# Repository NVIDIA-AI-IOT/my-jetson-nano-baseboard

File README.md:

# My Jetson Nano Baseboard

This basic baseboard gives the user the foundation and the flexibility to design their own baseboard for the Jetson Nano. It also repurposes some of the Jetson Nano’s interface signals for simple beginner projects.

This baseboard, as designed, contains:
* A 5V, 4A DC barrel jack
* 4 USB 2.0 connectors
* An HDMI connector
* A UART-to-USB bridge
* A debug USB
* A 40-pin GPIO
* A servo header
* Three user-interactive buttons (power, reset, and force recovery)
* A flex connector for an OLED display

Use these files to kickstart your own application-specific baseboard or implement some quick and easy projects!

## Quick Start

You only need a computer to get started right now! For a more in-depth setup guide, check out `docs/setup.md`.
1.	Install the appropriate version of KiCAD, an open source schematic and layout design program, for your operating system [here](https://www.kicad.org/download/).
1.	Download this GitHub repository either as a ZIP or on the command line.
1.	Save the following symbol and footprint libraries to the “Design Files/Libraries” folder (you may have to make an account – alternatively, if you want the practice, you could try making them yourself):
	1.	[B3SL-1002P](https://octopart.com/b3sl-1002p-omron-9515385)
	1.	[TPD4E02B04DQAR](https://www.snapeda.com/parts/TPD4E02B04DQAR/Texas%20Instruments/view-part/)
	1.	[3-1734592-0](https://www.te.com/usa-en/product-3-1734592-0.html)
	1.	[DC-005-2.0A](https://www.snapeda.com/parts/DC-005/Best%20Inc./view-part/)
	1.	[ACM2012-201-2P-T001](https://www.snapeda.com/parts/ACM2012-201-2P-T001/TDK/view-part/1217094/)
	1.	[10029449-111RLF](https://octopart.com/10029449-111rlf-amphenol+icc+%2F+fci-90332945#CadModels)
	1.	[2309413-1](https://www.te.com/usa-en/product-2309413-1.html)

1.	Open the project (.pro) file in KiCAD.
1.	Add the symbol and footprint libraries as project-specific to your KiCAD program, following [this guide](https://support.snapeda.com/en/articles/2651507-how-to-import-into-kicad). You will know that the libraries are correctly loaded when there are no more boxes with question marks.
1.	You are now set up to tinker with the files and launch your own hardware designs!

Be sure to download the Jetson Nano Product Design Guide [here](https://developer.nvidia.com/embedded/downloads) (NVIDIA Developer account required) to help you with your design.

If you want to make your boards and test them, you’ll need the Jetson Nano module (not included, can be bought as part of the developer kit [here](https://developer.nvidia.com/embedded/jetson-nano-developer-kit)). It is also helpful to have electronics equipment like an oscilloscope, a multimeter, and a soldering iron.

## Questions and Improvements

If you have a suggestion, please open an [issue](https://github.com/NVIDIA-AI-IOT/my-jetson-nano-baseboard/issues/new) on GitHub.

Please share your projects with us on the [Jetson Developer Forums](https://forums.developer.nvidia.com/c/agx-autonomous-machines/jetson-embedded-systems/70).

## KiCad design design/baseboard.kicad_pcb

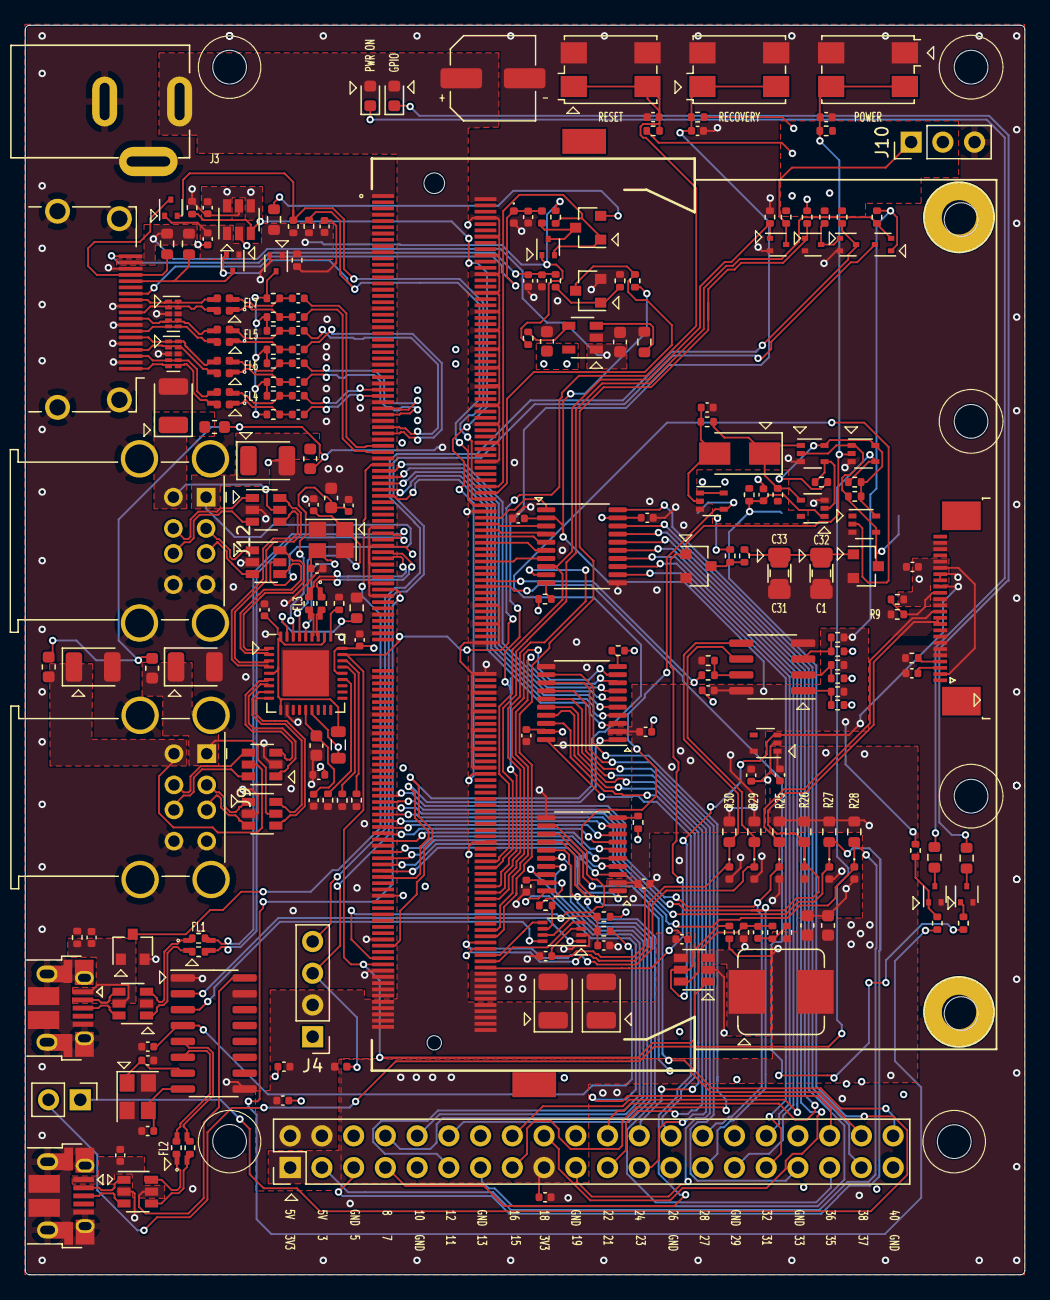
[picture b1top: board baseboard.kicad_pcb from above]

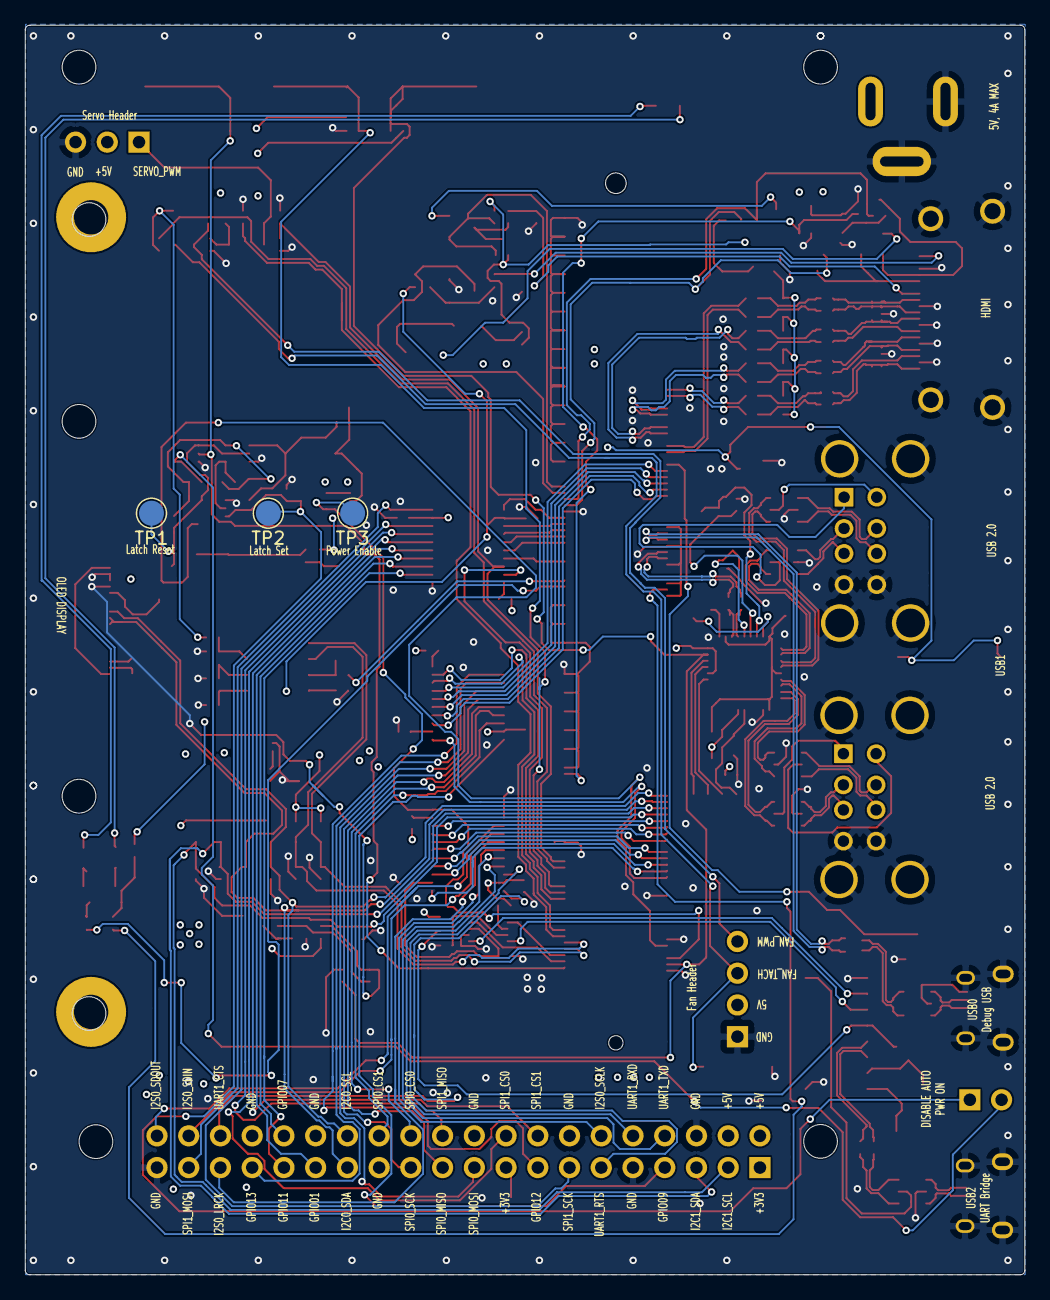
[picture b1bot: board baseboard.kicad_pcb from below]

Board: 4 copper layers, 80.0 x 100.0 mm, 240 parts (3 on the bottom side), 187 nets.

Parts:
C1, C31: 47uF; C_0805_2012Metric
C2, C8, C17: 4.7uF; C_0402_1005Metric
C3, C4, C18, C19: 1uF; C_0402_1005Metric
C10, C11, C12, C13, C14, C15, C16, C26, C27, C28, C29, C30, C36, C37, C38, C39, C40, C44, C46, C47, C48, C49, C50, C51, C52, C53, C54, C55, C56, C59, C60, C62, C63, C70: 0.1uF; C_0402_1005Metric
C20, C21, C72: 10uF; C_0603_1608Metric
C22, C23, C66, C67, C68, C69: 100uF; CP_EIA-3528-12_Kemet-T
C24: 330uF; C_Elec_6.3x7.7
C25: 6.8pF; C_0402_1005Metric
C32, C33: 47uF; C_1206_3216Metric
C41: 1nF; C_0402_1005Metric
C45, C61: 10nF; C_0603_1608Metric
C57, C58, C64, C65: 15pF; C_0402_1005Metric
C71: 0.1uF; C_0603_1608Metric
C73, C74: 33pF; C_0402_1005Metric
D1: SS14; D_SMA
D2, D5, D9, D10, D11, D20: USBLC6-2SC6; SOT-23-6
D4: BAS70-05; SOT-23
D6, D7: LED; LED_0603_1608Metric
D8, D12, D13, D14, D15, D16, D17: TPD1E10B06DPYR; D_0402_1005Metric
D18, D19: TPD4E02B04DQAR; USON-10_2.5x1.0mm_P0.5mm
FB1: Ferrite_Bead; L_0805_2012Metric
FL1, FL2, FL3, FL4, FL5, FL6, FL7: EMI_Filter_CommonMode; FIL_ACM2012-201-2P-T001
J1: Conn_01x02_Male; PinHeader_1x02_P2.54mm_Vertical
J2: Conn_01x24_Female; TE_2-1734839-4_1x24-1MP_P0.5mm_Horizontal
J3: Jack-DC; NINIGI_DC-005
J4: Conn_01x04_Male; PinHeader_1x04_P2.54mm_Vertical
J5: NANO-nvidia_nano; SODIMM-DDR4_8mm-NANO
J6: Conn_02x20_Odd_Even; PinHeader_2x20_P2.54mm_Vertical
J7, J8: USB_B_Micro; USB_Micro-B_Amphenol_10103594-0001LF_Horizontal
J9, J12: USB2.0_2Conn; USB_A_Wuerth_61400826021_Horizontal_Stacked
J10: Conn_01x03_Male; PinHeader_1x03_P2.54mm_Vertical
J11: HDMI_A; HDMI_A_Amphenol_10029449-111
L1: 2.2uH; L_Bourns_SRP7028A_7.3x6.6mm
L2: 1.2nH; L_0402_1005Metric
Q1, Q2, Q5: 2N7002; SOT-23
Q3, Q4, Q6, Q7, Q9, Q10, Q11, Q12, Q13, Q14: DMN26D0UT-7; SOT-523
Q8: MMBT3904; SOT-23
R1, R5, R6, R7, R13, R14, R15, R17, R20, R24, R33, R34, R35, R40, R50, R51, R52, R53, R54, R55, R56, R58, R71, R72, R79, R89, R90: 10k; R_0402_1005Metric
R2: 300k; R_0402_1005Metric
R3: 12k; R_0603_1608Metric
R4, R22: 4.7k; R_0402_1005Metric
R8, R31, R36, R41, R42, R44, R45, R46, R47, R48, R49, R57, R67, R68, R69, R70, R73, R74, R75, R76: 0; R_0402_1005Metric
R9, R23: 1k; R_0402_1005Metric
R10: 2.2k; R_0402_1005Metric
R11: 3.9k; R_0402_1005Metric
R12, R18, R19, R38, R82, R83, R84, R85, R86, R87, R88: 100k; R_0402_1005Metric
R16: 5.1k; R_0402_1005Metric
R21, R39: 100; R_0402_1005Metric
R25, R26, R27, R28, R29, R30: 2.2k; R_0603_1608Metric
R32, R37: 150; R_0603_1608Metric
R43: 1M; R_0402_1005Metric
R59, R60, R61, R62, R63, R64, R65, R66: 510; R_0402_1005Metric
R77, R78: 1.8k; R_0603_1608Metric
R80: 36k; R_0603_1608Metric
R81: 120k; R_0402_1005Metric
R91: 11k; R_0603_1608Metric
S1, S2, S3: B3SL-1022P; Crystal_SMD_7050-4Pin_7.0x5.0mm
TH1, TH2, TH3, TH4: Thermistor_PTC; Fuse_0603_1608Metric
TP1, TP2, TP3: TestPoint; TestPoint_Pad_D2.0mm
U1, U4: 74LVC1G126; SOT-353_SC-70-5
U2: 74LVC1G07GW; SOT-353_SC-70-5
U3, U24: MC74VHC1G01DFT1G; SOT-353_SC-70-5
U5, U6, U9: TXS0108EPW; TSSOP-20_4.4x6.5mm_P0.65mm
U7: TLV62569DDC; SOT-23-6
U8: TLV70018DCKT; SOT-353_SC-70-5
U10: MT9700; SOT-23-5
U15: TXB0102DCUR; VSSOP-8_2.3x2mm_P0.5mm
U16: CH340G; SOIC-16_3.9x9.9mm_P1.27mm
U18: AT24CS01-SSHM-T; SOIC-8_3.9x4.9mm_P1.27mm
U22: AP2281-3WG-7; SOT-23-6
U23: USB2514B-AEZG; QFN-36-1EP_6x6mm_P0.5mm_EP3.7x3.7mm
Y1: X322524MMB4SI; Crystal_SMD_3225-4Pin_3.2x2.5mm
Y2: X322512MSB4SI; Crystal_SMD_3225-4Pin_3.2x2.5mm

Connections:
3V3_PGOOD: J2.16, R24.2, U7.5, U8.3
+1V8: C10.1, C11.1, C14.1, C19.1, C29.1, C37.1, Q4.1, R14.1, R29.1, R30.1, R50.2, R52.2, R54.2, R79.1, R89.1, U5.2, U6.2, U8.5, U9.2, U15.3, U18.8
+3V3: C4.1, C12.1, C13.1, C16.1, C18.1, C20.1, C21.1, C30.1, C36.1, C60.1, C62.1, FB1.2, J2.2, J2.19, J2.20, J6.1, J6.17, L1.2, R10.2, R13.1, R15.1, R17.1, R21.1, R24.1, R25.1, R26.1, R27.1, R28.1, R40.1, R45.1, U5.19, U6.19, U8.1, U9.19, U22.4, U22.6, U23.15, U23.23, U23.27
+3V3_HDMI: C28.1, C56.1, Q10.1, Q11.1, Q13.1, Q14.1, R58.1, R71.1, R72.1, R80.2, R81.1, R90.1, U22.1
+5V: C15.1, C17.1, C22.1, C23.1, C24.1, C39.1, C71.1, D6.2, D7.2, J3.4, J4.2, J5.251, J5.252, J5.253, J5.254, J5.255, J5.256, J5.257, J5.258, J5.259, J5.260, J6.2, J6.4, J10.2, R1.1, R2.1, R4.1, R5.2, R6.1, R7.1, R16.1, R19.1, R20.1, R33.1, R34.1, R35.1, R38.1, TH1.2, TH2.2, TH3.2, TH4.2, U1.5, U2.5, U3.5, U4.1, U4.5, U7.4, U10.5, U24.5
+5V_HDMI: C72.1, J11.18, R77.2, R78.2, U10.1
/3.3V and 1.8V Power Supply/3V3BUCK_CAP_IN: C25.1, R21.2, R22.1
/3.3V and 1.8V Power Supply/3V3BUCK_FB: C25.2, R22.2, R23.1, U7.6
/3.3V and 1.8V Power Supply/3V3BUCK_SW: L1.1, U7.3
/HDMI Connections Part 1/HDMI_DDC_SCL_POL_CON: J11.15, Q11.3, R77.1
/HDMI Connections Part 1/HDMI_DDC_SDA_POL_CON: J11.16, Q13.3, R78.1
/HDMI Connections Part 1/HDMI_ON: Q10.3, R59.2, R60.2, R61.2, R62.2, R63.2, R64.2, R65.2, R66.2
/HDMI Connections Part 1/HDMI_TX0_CON_N: D19.4, D19.7, FL5.3, J11.9, R70.2
/HDMI Connections Part 1/HDMI_TX0_CON_P: D19.5, D19.6, FL5.4, J11.7, R69.2
/HDMI Connections Part 1/HDMI_TX0_FILT_N: C54.1, FL5.2, R61.1, R70.1
/HDMI Connections Part 1/HDMI_TX0_FILT_P: C50.1, FL5.1, R62.1, R69.1
/HDMI Connections Part 1/HDMI_TX1_CON_N: D18.1, D18.10, FL6.3, J11.6, R74.2
/HDMI Connections Part 1/HDMI_TX1_CON_P: D18.2, D18.9, FL6.4, J11.4, R73.2
/HDMI Connections Part 1/HDMI_TX1_FILT_N: C53.1, FL6.2, R63.1, R74.1
/HDMI Connections Part 1/HDMI_TX1_FILT_P: C49.1, FL6.1, R64.1, R73.1
/HDMI Connections Part 1/HDMI_TX2_CON_N: D18.4, D18.7, FL4.3, J11.3, R68.2
/HDMI Connections Part 1/HDMI_TX2_CON_P: D18.5, D18.6, FL4.4, J11.1, R67.2
/HDMI Connections Part 1/HDMI_TX2_FILT_N: C52.1, FL4.2, R65.1, R68.1
/HDMI Connections Part 1/HDMI_TX2_FILT_P: C48.1, FL4.1, R66.1, R67.1
/HDMI Connections Part 1/HDMI_TXC_CON_N: D19.1, D19.10, FL7.3, J11.12, R76.2
/HDMI Connections Part 1/HDMI_TXC_CON_P: D19.2, D19.9, FL7.4, J11.10, R75.2
/HDMI Connections Part 1/HDMI_TXC_FILT_N: C55.1, FL7.2, R59.1, R76.1
/HDMI Connections Part 1/HDMI_TXC_FILT_P: C51.1, FL7.1, R60.1, R75.1
/HDMI Connections Part 2/HDMI_PWR_EN: R90.2, U10.4
/HDMI Connections Part 2/HDMI_PWR_ILIM: R91.1, U10.3
/Level Shifters and GPIO Header/OE_UART_LVLSHIFT: R40.2, U15.6
/Level Shifters and GPIO Header/VCCB_UART_LVLSHIFT: C38.1, R44.2, R45.2, U15.7
/OLED Display/DATA_CMD: J2.15, R9.1, R10.1
/OLED Display/IREF: J2.4, R11.1
/OLED Display/OLED_COM_HI: C8.1, J2.3
/Power ON/OFF Logic/LATCH_RESET: Q2.3, R5.1, TP1.1, U1.1, U2.4, U3.2
/Power ON/OFF Logic/LATCH_SET: C2.1, J1.1, R4.2, TP2.1, U24.1
/Power ON/OFF Logic/POWER_EN_Q: D1.1, R6.2, R8.1, U3.1, U24.4
/Power ON/OFF Logic/POWER_EN_Q_NOT: R7.2, U3.4, U24.2
/Power ON/OFF Logic/POWER_EN_Q_R: C3.1, D1.2, R8.2, U4.2
/Power ON/OFF Logic/SHUTDOWN_Q2_G: C1.1, C31.1, C32.1, C33.1, Q2.1, R39.1
/Power ON/OFF Logic/SHUTDOWN_WAIT: Q1.3, R2.2, R39.2
/Power Regulation and Fan Tach/FAN_PWM_INV: Q3.1, Q12.3, R16.2
/Power Regulation and Fan Tach/FAN_PWM_LS: J4.4, Q3.3, R19.2
/Power Regulation and Fan Tach/FAN_TACH_IN: J4.3, Q4.3, R20.2
/SODIMM Connections Part 2/VIS_LED_OUT: D7.1, R37.1
/SODIMM Connections Part 2/VIS_SW_D: Q6.3, R37.2
/SODIMM Connections Part 2/VIS_SW_G: Q6.1, R36.2
/SODIMM Connections Part 3/FORCE_RECOVERY*: C46.1, J5.214, R35.2, S3.1, S3.2
/Servo Header and EEPROM/EEPROM_A0: R54.1, R55.2, U18.1
/Servo Header and EEPROM/EEPROM_A1: R52.1, R53.2, U18.2
/Servo Header and EEPROM/EEPROM_A2: R50.1, R51.2, U18.3
/Servo Header and EEPROM/WRITE_PROTEC: R56.2, R57.2, U18.7
/UART to USB Bridge/UART_XTAL_IN: C73.1, U16.7, Y2.1
/UART to USB Bridge/UART_XTAL_OUT: C74.1, U16.8, Y2.3
/UART to USB Bridge/USB2_DN: D9.1, D9.6, FL2.1, J8.2, R47.1
/UART to USB Bridge/USB2_DP: D9.3, D9.4, FL2.2, J8.3, R46.1
/UART to USB Bridge/USB2_FILT_N: FL2.4, R47.2, U16.6
/UART to USB Bridge/USB2_FILT_P: FL2.3, R46.2, U16.5
/UART to USB Bridge/VBUS_USB2: C44.1, D9.5, J8.1, U16.16
/USB2.0 Type A Hub/3V3_BEAD: C63.1, FB1.1, U23.5, U23.10, U23.29, U23.36
/USB2.0 Type A Hub/CFG_SEL0: R85.1, U23.24
/USB2.0 Type A Hub/CFG_SEL1: R86.1, U23.25
/USB2.0 Type A Hub/NON_REM0: R87.1, U23.28
/USB2.0 Type A Hub/NON_REM1: R88.1, U23.22
/USB2.0 Type A Hub/USB1_AP_N: FL3.4, R48.2, U23.30
/USB2.0 Type A Hub/USB1_AP_P: FL3.3, R49.2, U23.31
/USB2.0 Type A Hub/USB1_CR_FILT: C47.1, C61.1, U23.14
/USB2.0 Type A Hub/USB1_PLL_FILT: C45.1, C70.1, U23.34
/USB2.0 Type A Hub/USB1_XTAL_IN: C64.1, U23.33, Y1.1
/USB2.0 Type A Hub/USB1_XTAL_OUT: C65.1, U23.32, Y1.3
/USB2.0 Type A Hub/USB_DSP1_DN: D11.1, D11.6, J9.2, U23.8
/USB2.0 Type A Hub/USB_DSP1_DP: D11.3, D11.4, J9.3, U23.9
/USB2.0 Type A Hub/USB_DSP1_VBUS: C68.1, D11.5, J9.1, TH3.1
/USB2.0 Type A Hub/USB_DSP2_DN: D5.1, D5.6, J12.2, U23.1
/USB2.0 Type A Hub/USB_DSP2_DP: D5.3, D5.4, J12.3, U23.2
/USB2.0 Type A Hub/USB_DSP2_VBUS: C69.1, D5.5, J12.1, TH1.1
/USB2.0 Type A Hub/USB_DSP3_DN: D20.3, D20.4, J9.6, U23.6
/USB2.0 Type A Hub/USB_DSP3_DP: D20.1, D20.6, J9.7, U23.7
/USB2.0 Type A Hub/USB_DSP3_VBUS: C66.1, D20.5, J9.5, TH4.1
/USB2.0 Type A Hub/USB_DSP4_DN: D10.1, D10.6, J12.6, U23.3
/USB2.0 Type A Hub/USB_DSP4_DP: D10.3, D10.4, J12.7, U23.4
/USB2.0 Type A Hub/USB_DSP4_VBUS: C67.1, D10.5, J12.5, TH2.1
/uUSB Connections/USB0_FILT_N: D2.3, D2.4, FL1.1, J7.2, R42.1
/uUSB Connections/USB0_FILT_P: D2.1, D2.6, FL1.2, J7.3, R41.1
/uUSB Connections/VBUS_USB0: C40.1, D2.5, J7.1, Q5.1, R43.1
GND: C1.2, C2.2, C3.2, C4.2, C8.2, C10.2, C11.2, C12.2, C13.2, C14.2, C15.2, C16.2, C17.2, C18.2, C19.2, C20.2, C21.2, C22.2, C23.2, C24.2, C26.2, C27.2, C28.2, C29.2, C30.2, C31.2, C32.2, C33.2, C36.2, C37.2, C38.2, C39.2, C40.2, C41.2, C44.2, C45.2, C46.2, C47.2, C56.2, C57.2, C58.2, C59.2, C60.2, C61.2, C62.2, C63.2, C64.2, C65.2, C66.2, C67.2, C68.2, C69.2, C70.2, C71.2, C72.2, C73.2, C74.2, D2.2, D5.2, D8.2, D9.2, D10.2, D11.2, D12.2, D13.2, D14.2, D15.2, D16.2, D17.2, D18.3, D18.8, D19.3, D19.8, D20.2, J2.5, J2.6, J2.7, J2.8, J2.9, J2.13, J2.14, J2.17, J2.18, J2.22, J2.23, J3.2, J3.3, J4.1, J5.1, J5.2, J5.7, J5.8, J5.13, J5.14, J5.19, J5.20, J5.25, J5.26, J5.31, J5.32, J5.37, J5.38, J5.43, J5.44, J5.49, J5.50, J5.55, J5.56, J5.61, J5.62, J5.67, J5.68, J5.73, J5.74, J5.79, J5.80, J5.85, J5.86, J5.102, J5.107, J5.113, J5.119, J5.125, J5.129, J5.132, J5.135, J5.138, J5.141, J5.144, J5.146, J5.147, J5.152, J5.153, J5.158, J5.159, J5.164, J5.165, J5.170, J5.171, J5.176, J5.177, J5.200, J5.201, J5.217, J5.231, J5.241, J5.242, J5.243, J5.244, J5.245, J5.246, J5.247, J5.248, J5.249, J5.250, J6.6, J6.9, J6.14, J6.20, J6.25, J6.30, J6.34, J6.39, J7.5, J7.6, J8.5, J8.6, J9.4, J9.8, J9.9, J10.3, J11.2, J11.5, J11.8, J11.11, J11.17, J11.SH, J12.4, J12.8, J12.9, Q1.2, Q2.2, Q3.2, Q5.2, Q6.2, Q7.2, Q8.2, Q9.2, Q10.2, Q12.2, R3.2, R9.2, R11.2, R12.2, R18.2, R23.2, R43.2, R51.1, R53.1, R55.1, R56.1, R58.2, R82.2, R84.2, R85.2, R86.2, R87.2, R88.2, R91.2, S1.3, S1.4, S2.1, S2.2, S3.3, S3.4, U1.3, U2.3, U3.3, U4.3, U5.11, U6.11, U7.2, U8.2, U9.11, U10.2, U15.2, U16.1, U16.9, U16.15, U18.4, U22.2, U22.5, U23.11, U23.37, U24.3, Y1.2, Y1.4, Y2.2, Y2.4
GPIO00: J5.87, Q5.3
GPIO01: J5.118, U9.7
GPIO01_LS: J6.29, U9.14
GPIO02: J5.124, R57.1
GPIO03: J5.126, R36.1
GPIO04: J5.127, R31.1
GPIO07: J5.206, Q9.1, R18.1, U9.8
GPIO07_LS: J6.32, U9.13
GPIO08: J5.208, Q4.2, R14.2
GPIO09: J5.211, U5.1
GPIO09_LS: J6.7, U5.20
GPIO11: J5.216, U9.9
GPIO11_LS: J6.31, U9.12
GPIO12: J5.218, U5.9
GPIO12_LS: J6.15, U5.12
GPIO13: J5.228, U5.8
GPIO13_LS: J6.33, U5.13
GPIO14: J5.230, Q12.1, R12.1
HDMI_CEC: D4.1, J5.94, Q14.2, R81.2
HDMI_CEC_CON: C57.1, D8.1, J11.13, L2.2
HDMI_DDC_SCL_POL: J5.100, Q11.2, R71.2
HDMI_DDC_SDA_POL: J5.98, Q13.2, R72.2
HDMI_HPD: J5.96, Q8.3, R79.2
HDMI_HPD_CON: C58.1, C59.1, J11.19, R83.1
HDMI_TXC_N: C55.2, J5.81
HDMI_TXC_P: C51.2, J5.83
HDMI_TXD0_N: C54.2, J5.75
HDMI_TXD0_P: C50.2, J5.77
HDMI_TXD1_N: C53.2, J5.69
HDMI_TXD1_P: C49.2, J5.71
HDMI_TXD2_N: C52.2, J5.63
HDMI_TXD2_P: C48.2, J5.65
I2C0_SCL: D14.1, J2.12, J5.185, J6.28, R25.2
I2C0_SDA: D12.1, J2.10, J2.11, J5.187, J6.27, R26.2
I2C1_SCL: D13.1, J5.189, J6.5, R27.2
I2C1_SDA: D17.1, J5.191, J6.3, R28.2
I2C2_SCL: D15.1, J5.232, R29.2, U18.6
I2C2_SDA: D16.1, J5.234, R30.2, U18.5
I2S0_LRCK: J5.197, U6.7
I2S0_LRCK_LS: J6.35, U6.14
I2S0_SCLK: J5.199, U6.6
I2S0_SCLK_LS: J6.12, U6.15
I2S0_SDIN: J5.195, U6.8
I2S0_SDIN_LS: J6.38, U6.13
I2S0_SDOUT: J5.193, U6.9
I2S0_SDOUT_LS: J6.40, U6.12
MOD_SLEEP*: J5.178, R84.1, U22.3
unnamed: D4.2, R80.1
unnamed: D4.3, L2.1, Q14.3
unnamed: D6.1, R32.1
unnamed: J1.2, R1.2, U1.4
unnamed: Q7.1, R31.2, R89.2
unnamed: Q7.3, R32.2
unnamed: Q8.1, R82.1, R83.2
unnamed: R3.1, U23.35
unnamed: R13.2, U5.10
unnamed: R15.2, U6.10
unnamed: R17.2, U9.10
POWER_EN: J5.237, TP3.1, U4.4
REGOUT_3V3: C41.1, R44.1, U16.4
SERVO_PWM: J10.1, Q9.3, R38.2
SHUTDOWN_REQ*: J5.233, U2.2
SLEEP_WAKE*: C27.1, J5.240, Q1.1, R34.2, S2.3, S2.4, U1.2
SPI0_CS0: J5.95, U5.4
SPI0_CS0_LS: J6.24, U5.17
SPI0_CS1: J5.97, U5.3
SPI0_CS1_LS: J6.26, U5.18
SPI0_MISO: J5.93, U5.5
SPI0_MISO_LS: J6.21, U5.16
SPI0_MOSI: J5.89, U5.7
SPI0_MOSI_LS: J6.19, U5.14
SPI0_SCK: J5.91, U5.6
SPI0_SCK_LS: J6.23, U5.15
SPI1_CS0: J5.110, U9.5
SPI1_CS0_LS: J6.18, U9.16
SPI1_CS1: J5.112, U9.6
SPI1_CS1_LS: J6.16, U9.15
SPI1_MISO: J5.108, U9.4
SPI1_MISO_LS: J6.22, U9.17
SPI1_MOSI: J5.104, U9.1
SPI1_MOSI_LS: J6.37, U9.20
SPI1_SCK: J5.106, U9.3
SPI1_SCK_LS: J6.13, U9.18
SYS_RESET*: C26.1, J5.239, R33.2, S1.1, S1.2, U7.1, U23.26
UART1_CTS: J5.209, U6.1
UART1_CTS_LS: J6.36, U6.20
UART1_RTS: J5.207, U6.3
UART1_RTS_LS: J6.11, U6.18
UART1_RXD: J5.205, U6.4
UART1_RXD_LS: J6.10, U6.17
UART1_TXD: J5.203, U6.5
UART1_TXD_LS: J6.8, U6.16
UART2_RXD: J5.238, U15.4
UART2_RXD_3v3: U15.1, U16.2
UART2_TXD: J5.236, U15.5
UART2_TXD_3v3: U15.8, U16.3
USB0_D_N: FL1.4, J5.109, R42.2
USB0_D_P: FL1.3, J5.111, R41.2
USB1_D_N: FL3.1, J5.115, R48.1
USB1_D_P: FL3.2, J5.117, R49.1

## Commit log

2018-01-28 add i2c functional script from val
2018-01-28 validation scripts after testing
2021-07-07 add initial files
2021-07-07 add links to README.md
2021-07-07 fix numbering
2021-07-07 add design and manufacturing files
2021-07-08 add i2c testing script, delete models
2021-07-08 debugging i2c script
2021-07-08 change mega to kilo
2021-07-09 add schematic to docs file
2021-07-09 add files to docs folder'
2021-07-09 add spi skeleton
2021-07-13 add documentation and sample project scripts
2021-07-16 add i2s script
2021-07-16 write validation scripts
2021-07-19 add validation scripts
2021-07-19 use open source filetypes
2021-07-19 add copyright notices to all code
2021-07-20 usability changes
2021-07-20 fix readme changes
2021-07-20 usability
2021-07-20 add validation to docs
2021-07-26 Add CAD for potential OLED support
2021-07-28 Update files for A01
2021-07-28 rename baseboard
2021-07-28 update docs'
2021-08-11 remove USB footprint
2021-08-11 add final board pictures
2021-08-11 edit photo names
2021-08-11 add images
2021-08-12 update A01 files
2021-08-12 rename & move files for cohesion
2021-08-12 update docs
2021-08-12 rename A00 files
2021-08-13 Rename os_baseboard-top-pos.csv to assemble-top-pos.csv
